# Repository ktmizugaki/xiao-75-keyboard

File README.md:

# xiao 75% keyboard

* 86 Kailh mini choc switches for keyboard keys.
* 2 Kailh X Switches for mouse buttons.
* 1 Top-up JT8P analog stick for pointing device.
* Seeed XIAO as controller.

Here is layout of xiao 75% keyboard. Darker key indicates keys with 1.25u keycap.  

I don't use `Caps Lock` key, and replaced it by `Left Control` key.

# Required parts

## Keyboard main

* 86x [Kailh PG1232 mini choc switch](https://www.aliexpress.com/item/4000277394324.html)
  * keyboard switches
* 2x [Kailh PG1425 X switch](https://www.aliexpress.com/item/32985602923.html)
  * mouse buttons
* 1x [TOP-UP JT8P-3.2T-B10K-1-16Y](https://akizukidenshi.com/catalog/g/gP-04048)
  * pointing device
* 1x [Seeed XIAO](https://akizukidenshi.com/catalog/g/gM-15178)
  * Seeed XIAO
* 88x [1N4148W](https://akizukidenshi.com/catalog/g/gI-07084)
  * SOD-123 SMD switching diode
* 4x [SS2040FL](https://akizukidenshi.com/catalog/g/gI-02073)
  * SOD-123 SMD low Vf diode
* 10x [1608Metric 560ohm SMD resistor](https://www.sengoku.co.jp/mod/sgk_cart/detail.php?code=EEHD-57GE)
* 10x [1SS355VM](https://akizukidenshi.com/catalog/g/gI-05866)
  * SOD-323 SMD switching diode
* 2x [7P pin socket](https://akizukidenshi.com/catalog/g/gP-01014)
* 1x [14P pin header](https://akizukidenshi.com/catalog/g/gC-04397)
  * split to 2x 7P pin heaeder
* 1x Keyboard PCB

## Backlight LED
* 86x [2012Metric SMD LED](https://akizukidenshi.com/catalog/g/gI-06422)
* 86x [2012Metric 2.2k ohm SMD resistor](https://www.sengoku.co.jp/mod/sgk_cart/detail.php?code=EEHD-57C4)
  * Adjust value depending on Vf of LED
* 1x [NJM12888-33](https://akizukidenshi.com/catalog/g/gI-10675)
  * SOT23-5 Voltage Regulator with enable pin
* 2x [2012Metric 0.1uF SMD capacitor](https://akizukidenshi.com/catalog/g/gP-00349)
* 1x [2012Metric 1uF SMD capacitor](https://akizukidenshi.com/catalog/g/gP-09174)
* 1x [6011S1M1 slide switch](https://akizukidenshi.com/catalog/g/gP-15365)
  * Turn on/off LEDs

# About firmware

Source code of Arduino based firmware is available under [prog](prog)

Supports only SAMD21 version of XIAO.

See [prog/README.md](prog/README.md) for details.

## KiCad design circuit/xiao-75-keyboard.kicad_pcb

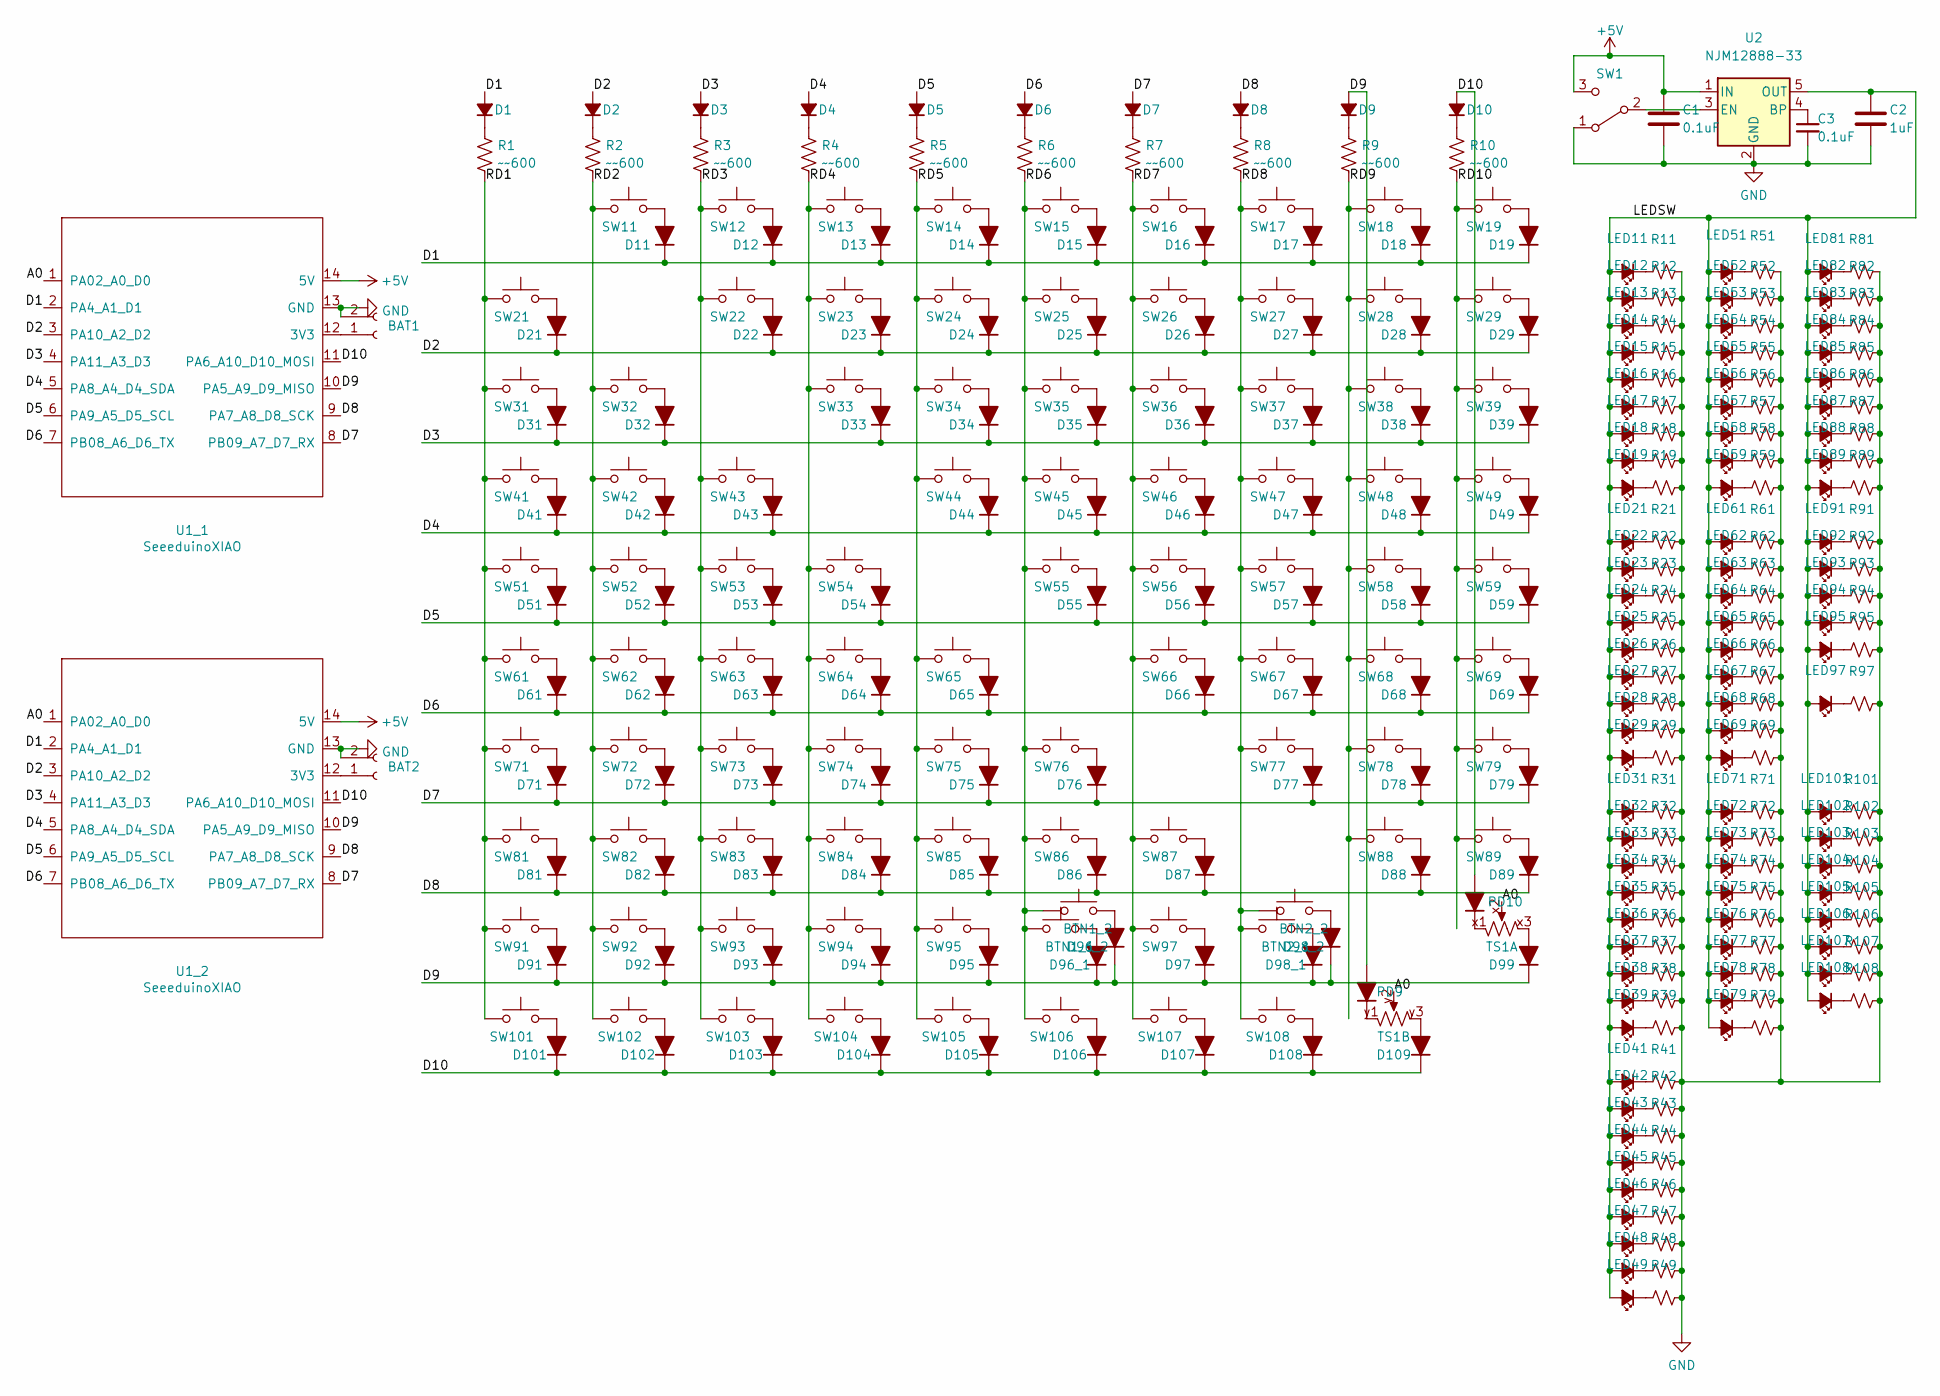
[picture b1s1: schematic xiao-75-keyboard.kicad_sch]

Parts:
BAT1, BAT2: BLEMicroPro_Battery
BTN1_1, BTN1_2: BUTTON1; Kailh_X_Switch_PG1425
BTN2_1, BTN2_2: BUTTON2; Kailh_X_Switch_PG1425
C1, C3: 0.1uF; C_0805_2012Metric_Pad1.18x1.45mm_HandSolder
C2: 1uF; C_0805_2012Metric_Pad1.18x1.45mm_HandSolder
D1, D2, D3, D4, D5, D6, D7, D8, D9, D10: 1SS355VM; D_0603_1608Metric_Pad1.05x0.95mm_HandSolder
D11, D12, D13, D14, D15, D16, D17, D18, D19, D21, D22, D23, D24, D25, D26, D27, D28, D29, D31, D32, D33, D34, D35, D36, D37, D38, D39, D41, D42, D43, D44, D45, D46, D47, D48, D49, D51, D52, D53, D54, D55, D56, D57, D58, D59, D61, D62, D63, D64, D65, D66, D67, D68, D69, D71, D72, D73, D74, D75, D76, D77, D78, D79, D81, D82, D83, D84, D85, D86, D87, D88, D89, D91, D92, D93, D94, D95, D96_1, D96_2, D97, D98_1, D98_2, D101, D102, D103, D104, D105, D106, D107, D108: 1N4148W; D_SOD-123
D99, D109: SS2040FL; D_SOD-123
LED11, LED12, LED13, LED14, LED15, LED16, LED17, LED18, LED19, LED21, LED22, LED23, LED24, LED25, LED26, LED27, LED28, LED29, LED31, LED32, LED33, LED34, LED35, LED36, LED37, LED38, LED39, LED41, LED42, LED43, LED44, LED45, LED46, LED47, LED48, LED49, LED51, LED52, LED53, LED54, LED55, LED56, LED57, LED58, LED59, LED61, LED62, LED63, LED64, LED65, LED66, LED67, LED68, LED69, LED71, LED72, LED73, LED74, LED75, LED76, LED77, LED78, LED79, LED81, LED82, LED83, LED84, LED85, LED86, LED87, LED88, LED89, LED91, LED92, LED93, LED94, LED95, LED97, LED101, LED102, LED103, LED104, LED105, LED106, LED107, LED108: 2012; LED_0805_2012Metric_Pad1.15x1.40mm_HandSolder
PD9, PD10: SS2040FL; D_SOD-123
R1, R2, R3, R4, R5, R6, R7, R8, R9, R10: ~~600; R_0603_1608Metric_Pad1.05x0.95mm_HandSolder
R11, R12, R13, R14, R15, R16, R17, R18, R19, R21, R22, R23, R24, R25, R26, R27, R28, R29, R31, R32, R33, R34, R35, R36, R37, R38, R39, R41, R42, R43, R44, R45, R46, R47, R48, R49, R51, R52, R53, R54, R55, R56, R57, R58, R59, R61, R62, R63, R64, R65, R66, R67, R68, R69, R71, R72, R73, R74, R75, R76, R77, R78, R79, R81, R82, R83, R84, R85, R86, R87, R88, R89, R91, R92, R93, R94, R95, R97, R101, R102, R103, R104, R105, R106, R107, R108: 1.5kΩ; R_0805_2012Metric_Pad1.20x1.40mm_HandSolder
SW1: 6011S1M1RE-G
SW11: ESC; Kailh_Choc_Univ
SW12: F1; Kailh_Choc_Univ
SW13: F2; Kailh_Choc_Univ
SW14: F3; Kailh_Choc_Univ
SW15: F4; Kailh_Choc_Univ
SW16: %/5; Kailh_Choc_Univ
SW17: F5; Kailh_Choc_Univ
SW18: ^/6; Kailh_Choc_Univ
SW19: F6; Kailh_Choc_Univ
SW21: Home; Kailh_Choc_Univ
SW22: DEL; Kailh_Choc_Univ
SW23: F12; Kailh_Choc_Univ
SW24: F11; Kailh_Choc_Univ
SW25: F10; Kailh_Choc_Univ
SW26: F9; Kailh_Choc_Univ
SW27: F8; Kailh_Choc_Univ
SW28: F7; Kailh_Choc_Univ
SW29: &/7; Kailh_Choc_Univ
SW31: !/1; Kailh_Choc_Univ
SW32: ~/`; Kailh_Choc_Univ
SW33: @/2; Kailh_Choc_Univ
SW34: #/3; Kailh_Choc_Univ
SW35: E; Kailh_Choc_Univ
SW36: $/4; Kailh_Choc_Univ
SW37: R; Kailh_Choc_Univ
SW38: T; Kailh_Choc_Univ
SW39: Y; Kailh_Choc_Univ
SW41: PgUp; Kailh_Choc_Univ
SW42: |/\; Kailh_Choc_Univ
SW43: BS; Kailh_Choc_Univ
SW44: +/=; Kailh_Choc_Univ
SW45: _/-; Kailh_Choc_Univ
SW46: )/0; Kailh_Choc_Univ
SW47: (/9; Kailh_Choc_Univ
SW48: */8; Kailh_Choc_Univ
SW49: U; Kailh_Choc_Univ
SW51: Q; Kailh_Choc_Univ
SW52: TAB; Kailh_Choc_Univ
SW53: W; Kailh_Choc_Univ
SW54: S; Kailh_Choc_Univ
SW55: D; Kailh_Choc_Univ
SW56: F; Kailh_Choc_Univ
SW57: G; Kailh_Choc_Univ
SW58: H; Kailh_Choc_Univ
SW59: N; Kailh_Choc_Univ
SW61: PgDn; Kailh_Choc_Univ
SW62: Enter; Kailh_Choc_Univ
SW63: }/]; Kailh_Choc_Univ
SW64: {/[; Kailh_Choc_Univ
SW65: P; Kailh_Choc_Univ
SW66: O; Kailh_Choc_Univ
SW67: K; Kailh_Choc_Univ
SW68: I; Kailh_Choc_Univ
SW69: J; Kailh_Choc_Univ
SW71: A; Kailh_Choc_Univ
SW72: CapsLock; Kailh_Choc_Univ
SW73: Z; Kailh_Choc_Univ
SW74: X; Kailh_Choc_Univ
SW75: C; Kailh_Choc_Univ
SW76: V; Kailh_Choc_Univ
SW77: B; Kailh_Choc_Univ
SW78, SW97: Space; Kailh_Choc_Univ
SW79: Alt_R; Kailh_Choc_Univ
SW81: End; Kailh_Choc_Univ
SW82: UP; Kailh_Choc_Univ
SW83: Shift_R; Kailh_Choc_Univ
SW84: "/'; Kailh_Choc_Univ
SW85: ?//; Kailh_Choc_Univ
SW86: :/;; Kailh_Choc_Univ
SW87: L; Kailh_Choc_Univ
SW88: </,; Kailh_Choc_Univ
SW89: M; Kailh_Choc_Univ
SW91: Ctrl_L; Kailh_Choc_Univ
SW92: Shift_L; Kailh_Choc_Univ
SW93: Fn; Kailh_Choc_Univ
SW94: Win_L; Kailh_Choc_Univ
SW95: Alt_L; Kailh_Choc_Univ
SW101: RIGHT; Kailh_Choc_Univ
SW102: DOWN; Kailh_Choc_Univ
SW103: LEFT; Kailh_Choc_Univ
SW104: Ctrl_R; Kailh_Choc_Univ
SW105: Fn2; Kailh_Choc_Univ
SW106: >/.; Kailh_Choc_Univ
SW107: App; Kailh_Choc_Univ
SW108: Win_R; Kailh_Choc_Univ
TS1: JT8P-3.2T-B10K-1-16Y-2; JT8P-3.2T-B10K-1-16Y
U1_1, U1_2: SeeeduinoXIAO; Seeeduino_XIAO_THT_UpsideDown
U2: NJM12888-33; SOT-23-5

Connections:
+5V: C1.1, SW1.3 (C), U1_1.14 (5V), U1_2.14 (5V), U2.1 (IN)
/A0: TS1.x2 (X), TS1.y2 (Y), U1_1.1 (PA02_A0_D0), U1_2.1 (PA02_A0_D0)
/D1: D1.2 (A), D11.1 (K), D12.1 (K), D13.1 (K), D14.1 (K), D15.1 (K), D16.1 (K), D17.1 (K), D18.1 (K), D19.1 (K), U1_1.2 (PA4_A1_D1), U1_2.2 (PA4_A1_D1)
/D2: D2.2 (A), D21.1 (K), D22.1 (K), D23.1 (K), D24.1 (K), D25.1 (K), D26.1 (K), D27.1 (K), D28.1 (K), D29.1 (K), U1_1.3 (PA10_A2_D2), U1_2.3 (PA10_A2_D2)
/D3: D3.2 (A), D31.1 (K), D32.1 (K), D33.1 (K), D34.1 (K), D35.1 (K), D36.1 (K), D37.1 (K), D38.1 (K), D39.1 (K), U1_1.4 (PA11_A3_D3), U1_2.4 (PA11_A3_D3)
/D4: D4.2 (A), D41.1 (K), D42.1 (K), D43.1 (K), D44.1 (K), D45.1 (K), D46.1 (K), D47.1 (K), D48.1 (K), D49.1 (K), U1_1.5 (PA8_A4_D4_SDA), U1_2.5 (PA8_A4_D4_SDA)
/D5: D5.2 (A), D51.1 (K), D52.1 (K), D53.1 (K), D54.1 (K), D55.1 (K), D56.1 (K), D57.1 (K), D58.1 (K), D59.1 (K), U1_1.6 (PA9_A5_D5_SCL), U1_2.6 (PA9_A5_D5_SCL)
/D6: D6.2 (A), D61.1 (K), D62.1 (K), D63.1 (K), D64.1 (K), D65.1 (K), D66.1 (K), D67.1 (K), D68.1 (K), D69.1 (K), U1_1.7 (PB08_A6_D6_TX), U1_2.7 (PB08_A6_D6_TX)
/D7: D7.2 (A), D71.1 (K), D72.1 (K), D73.1 (K), D74.1 (K), D75.1 (K), D76.1 (K), D77.1 (K), D78.1 (K), D79.1 (K), U1_1.8 (PB09_A7_D7_RX), U1_2.8 (PB09_A7_D7_RX)
/D8: D8.2 (A), D81.1 (K), D82.1 (K), D83.1 (K), D84.1 (K), D85.1 (K), D86.1 (K), D87.1 (K), D88.1 (K), D89.1 (K), U1_1.9 (PA7_A8_D8_SCK), U1_2.9 (PA7_A8_D8_SCK)
/D9: D9.2 (A), D91.1 (K), D92.1 (K), D93.1 (K), D94.1 (K), D95.1 (K), D96_1.1 (K), D96_2.1 (K), D97.1 (K), D98_1.1 (K), D98_2.1 (K), D99.1 (K), PD9.2 (A), U1_1.10 (PA5_A9_D9_MISO), U1_2.10 (PA5_A9_D9_MISO)
/D10: D10.2 (A), D101.1 (K), D102.1 (K), D103.1 (K), D104.1 (K), D105.1 (K), D106.1 (K), D107.1 (K), D108.1 (K), D109.1 (K), PD10.2 (A), U1_1.11 (PA6_A10_D10_MOSI), U1_2.11 (PA6_A10_D10_MOSI)
/LEDSW: C2.1, LED11.2 (A), LED12.2 (A), LED13.2 (A), LED14.2 (A), LED15.2 (A), LED16.2 (A), LED17.2 (A), LED18.2 (A), LED19.2 (A), LED21.2 (A), LED22.2 (A), LED23.2 (A), LED24.2 (A), LED25.2 (A), LED26.2 (A), LED27.2 (A), LED28.2 (A), LED29.2 (A), LED31.2 (A), LED32.2 (A), LED33.2 (A), LED34.2 (A), LED35.2 (A), LED36.2 (A), LED37.2 (A), LED38.2 (A), LED39.2 (A), LED41.2 (A), LED42.2 (A), LED43.2 (A), LED44.2 (A), LED45.2 (A), LED46.2 (A), LED47.2 (A), LED48.2 (A), LED49.2 (A), LED51.2 (A), LED52.2 (A), LED53.2 (A), LED54.2 (A), LED55.2 (A), LED56.2 (A), LED57.2 (A), LED58.2 (A), LED59.2 (A), LED61.2 (A), LED62.2 (A), LED63.2 (A), LED64.2 (A), LED65.2 (A), LED66.2 (A), LED67.2 (A), LED68.2 (A), LED69.2 (A), LED71.2 (A), LED72.2 (A), LED73.2 (A), LED74.2 (A), LED75.2 (A), LED76.2 (A), LED77.2 (A), LED78.2 (A), LED79.2 (A), LED81.2 (A), LED82.2 (A), LED83.2 (A), LED84.2 (A), LED85.2 (A), LED86.2 (A), LED87.2 (A), LED88.2 (A), LED89.2 (A), LED91.2 (A), LED92.2 (A), LED93.2 (A), LED94.2 (A), LED95.2 (A), LED97.2 (A), LED101.2 (A), LED102.2 (A), LED103.2 (A), LED104.2 (A), LED105.2 (A), LED106.2 (A), LED107.2 (A), LED108.2 (A), U2.5 (OUT)
/RD1: R1.2, SW21.1, SW31.1, SW41.1, SW51.1, SW61.1, SW71.1, SW81.1, SW91.1, SW101.1
/RD2: R2.2, SW11.1, SW32.1, SW42.1, SW52.1, SW62.1, SW72.1, SW82.1, SW92.1, SW102.1
/RD3: R3.2, SW12.1, SW22.1, SW43.1, SW53.1, SW63.1, SW73.1, SW83.1, SW93.1, SW103.1
/RD4: R4.2, SW13.1, SW23.1, SW33.1, SW54.1, SW64.1, SW74.1, SW84.1, SW94.1, SW104.1
/RD5: R5.2, SW14.1, SW24.1, SW34.1, SW44.1, SW65.1, SW75.1, SW85.1, SW95.1, SW105.1
/RD6: BTN1_1.2, BTN1_2.2, R6.2, SW15.1, SW25.1, SW35.1, SW45.1, SW55.1, SW76.1, SW86.1, SW106.1
/RD7: R7.2, SW16.1, SW26.1, SW36.1, SW46.1, SW56.1, SW66.1, SW87.1, SW97.1, SW107.1
/RD8: BTN2_1.2, BTN2_2.2, R8.2, SW17.1, SW27.1, SW37.1, SW47.1, SW57.1, SW67.1, SW77.1, SW108.1
/RD9: R9.2, SW18.1, SW28.1, SW38.1, SW48.1, SW58.1, SW68.1, SW78.1, SW88.1
/RD10: R10.2, SW19.1, SW29.1, SW39.1, SW49.1, SW59.1, SW69.1, SW79.1, SW89.1
GND: BAT1.2, BAT2.2, C1.2, C2.2, C3.2, R11.2, R12.2, R13.2, R14.2, R15.2, R16.2, R17.2, R18.2, R19.2, R21.2, R22.2, R23.2, R24.2, R25.2, R26.2, R27.2, R28.2, R29.2, R31.2, R32.2, R33.2, R34.2, R35.2, R36.2, R37.2, R38.2, R39.2, R41.2, R42.2, R43.2, R44.2, R45.2, R46.2, R47.2, R48.2, R49.2, R51.2, R52.2, R53.2, R54.2, R55.2, R56.2, R57.2, R58.2, R59.2, R61.2, R62.2, R63.2, R64.2, R65.2, R66.2, R67.2, R68.2, R69.2, R71.2, R72.2, R73.2, R74.2, R75.2, R76.2, R77.2, R78.2, R79.2, R81.2, R82.2, R83.2, R84.2, R85.2, R86.2, R87.2, R88.2, R89.2, R91.2, R92.2, R93.2, R94.2, R95.2, R97.2, R101.2, R102.2, R103.2, R104.2, R105.2, R106.2, R107.2, R108.2, SW1.1 (A), U1_1.13 (GND), U1_2.13 (GND), U2.2 (GND)
unnamed: BAT1.1, U1_1.12 (3V3)
unnamed: BAT2.1, U1_2.12 (3V3)
unnamed: BTN1_1.1, D96_1.2 (A)
unnamed: BTN1_2.1, D96_2.2 (A)
unnamed: BTN2_1.1, D98_1.2 (A)
unnamed: BTN2_2.1, D98_2.2 (A)
unnamed: C3.1, U2.4 (BP)
unnamed: D1.1 (K), R1.1
unnamed: D2.1 (K), R2.1
unnamed: D3.1 (K), R3.1
unnamed: D4.1 (K), R4.1
unnamed: D5.1 (K), R5.1
unnamed: D6.1 (K), R6.1
unnamed: D7.1 (K), R7.1
unnamed: D8.1 (K), R8.1
unnamed: D9.1 (K), R9.1
unnamed: D10.1 (K), R10.1
unnamed: D11.2 (A), SW11.2
unnamed: D12.2 (A), SW12.2
unnamed: D13.2 (A), SW13.2
unnamed: D14.2 (A), SW14.2
unnamed: D15.2 (A), SW15.2
unnamed: D16.2 (A), SW16.2
unnamed: D17.2 (A), SW17.2
unnamed: D18.2 (A), SW18.2
unnamed: D19.2 (A), SW19.2
unnamed: D21.2 (A), SW21.2
unnamed: D22.2 (A), SW22.2
unnamed: D23.2 (A), SW23.2
unnamed: D24.2 (A), SW24.2
unnamed: D25.2 (A), SW25.2
unnamed: D26.2 (A), SW26.2
unnamed: D27.2 (A), SW27.2
unnamed: D28.2 (A), SW28.2
unnamed: D29.2 (A), SW29.2
unnamed: D31.2 (A), SW31.2
unnamed: D32.2 (A), SW32.2
unnamed: D33.2 (A), SW33.2
unnamed: D34.2 (A), SW34.2
unnamed: D35.2 (A), SW35.2
unnamed: D36.2 (A), SW36.2
unnamed: D37.2 (A), SW37.2
unnamed: D38.2 (A), SW38.2
unnamed: D39.2 (A), SW39.2
unnamed: D41.2 (A), SW41.2
unnamed: D42.2 (A), SW42.2
unnamed: D43.2 (A), SW43.2
unnamed: D44.2 (A), SW44.2
unnamed: D45.2 (A), SW45.2
unnamed: D46.2 (A), SW46.2
unnamed: D47.2 (A), SW47.2
unnamed: D48.2 (A), SW48.2
unnamed: D49.2 (A), SW49.2
unnamed: D51.2 (A), SW51.2
unnamed: D52.2 (A), SW52.2
unnamed: D53.2 (A), SW53.2
unnamed: D54.2 (A), SW54.2
unnamed: D55.2 (A), SW55.2
unnamed: D56.2 (A), SW56.2
unnamed: D57.2 (A), SW57.2
unnamed: D58.2 (A), SW58.2
unnamed: D59.2 (A), SW59.2
unnamed: D61.2 (A), SW61.2
unnamed: D62.2 (A), SW62.2
unnamed: D63.2 (A), SW63.2
unnamed: D64.2 (A), SW64.2
unnamed: D65.2 (A), SW65.2
unnamed: D66.2 (A), SW66.2
unnamed: D67.2 (A), SW67.2
unnamed: D68.2 (A), SW68.2
unnamed: D69.2 (A), SW69.2
unnamed: D71.2 (A), SW71.2
unnamed: D72.2 (A), SW72.2
unnamed: D73.2 (A), SW73.2
unnamed: D74.2 (A), SW74.2
unnamed: D75.2 (A), SW75.2
unnamed: D76.2 (A), SW76.2
unnamed: D77.2 (A), SW77.2
unnamed: D78.2 (A), SW78.2
unnamed: D79.2 (A), SW79.2
unnamed: D81.2 (A), SW81.2
unnamed: D82.2 (A), SW82.2
unnamed: D83.2 (A), SW83.2
unnamed: D84.2 (A), SW84.2
unnamed: D85.2 (A), SW85.2
unnamed: D86.2 (A), SW86.2
unnamed: D87.2 (A), SW87.2
unnamed: D88.2 (A), SW88.2
unnamed: D89.2 (A), SW89.2
unnamed: D91.2 (A), SW91.2
unnamed: D92.2 (A), SW92.2
unnamed: D93.2 (A), SW93.2
unnamed: D94.2 (A), SW94.2
unnamed: D95.2 (A), SW95.2
unnamed: D97.2 (A), SW97.2
unnamed: D99.2 (A), TS1.x3 (GND)
unnamed: D101.2 (A), SW101.2
unnamed: D102.2 (A), SW102.2
unnamed: D103.2 (A), SW103.2
unnamed: D104.2 (A), SW104.2
unnamed: D105.2 (A), SW105.2
unnamed: D106.2 (A), SW106.2
unnamed: D107.2 (A), SW107.2
unnamed: D108.2 (A), SW108.2
unnamed: D109.2 (A), TS1.y3 (GND)
unnamed: LED11.1 (K), R11.1
unnamed: LED12.1 (K), R12.1
unnamed: LED13.1 (K), R13.1
unnamed: LED14.1 (K), R14.1
unnamed: LED15.1 (K), R15.1
unnamed: LED16.1 (K), R16.1
unnamed: LED17.1 (K), R17.1
unnamed: LED18.1 (K), R18.1
unnamed: LED19.1 (K), R19.1
unnamed: LED21.1 (K), R21.1
unnamed: LED22.1 (K), R22.1
unnamed: LED23.1 (K), R23.1
unnamed: LED24.1 (K), R24.1
unnamed: LED25.1 (K), R25.1
unnamed: LED26.1 (K), R26.1
unnamed: LED27.1 (K), R27.1
unnamed: LED28.1 (K), R28.1
unnamed: LED29.1 (K), R29.1
unnamed: LED31.1 (K), R31.1
unnamed: LED32.1 (K), R32.1
unnamed: LED33.1 (K), R33.1
unnamed: LED34.1 (K), R34.1
unnamed: LED35.1 (K), R35.1
unnamed: LED36.1 (K), R36.1
unnamed: LED37.1 (K), R37.1
unnamed: LED38.1 (K), R38.1
unnamed: LED39.1 (K), R39.1
unnamed: LED41.1 (K), R41.1
unnamed: LED42.1 (K), R42.1
unnamed: LED43.1 (K), R43.1
unnamed: LED44.1 (K), R44.1
unnamed: LED45.1 (K), R45.1
unnamed: LED46.1 (K), R46.1
unnamed: LED47.1 (K), R47.1
unnamed: LED48.1 (K), R48.1
unnamed: LED49.1 (K), R49.1
unnamed: LED51.1 (K), R51.1
unnamed: LED52.1 (K), R52.1
unnamed: LED53.1 (K), R53.1
unnamed: LED54.1 (K), R54.1
unnamed: LED55.1 (K), R55.1
unnamed: LED56.1 (K), R56.1
unnamed: LED57.1 (K), R57.1
unnamed: LED58.1 (K), R58.1
unnamed: LED59.1 (K), R59.1
unnamed: LED61.1 (K), R61.1
unnamed: LED62.1 (K), R62.1
unnamed: LED63.1 (K), R63.1
unnamed: LED64.1 (K), R64.1
unnamed: LED65.1 (K), R65.1
unnamed: LED66.1 (K), R66.1
unnamed: LED67.1 (K), R67.1
unnamed: LED68.1 (K), R68.1
unnamed: LED69.1 (K), R69.1
unnamed: LED71.1 (K), R71.1
unnamed: LED72.1 (K), R72.1
unnamed: LED73.1 (K), R73.1
unnamed: LED74.1 (K), R74.1
unnamed: LED75.1 (K), R75.1
unnamed: LED76.1 (K), R76.1
unnamed: LED77.1 (K), R77.1
unnamed: LED78.1 (K), R78.1
unnamed: LED79.1 (K), R79.1
unnamed: LED81.1 (K), R81.1
unnamed: LED82.1 (K), R82.1
unnamed: LED83.1 (K), R83.1
unnamed: LED84.1 (K), R84.1
unnamed: LED85.1 (K), R85.1
unnamed: LED86.1 (K), R86.1
unnamed: LED87.1 (K), R87.1
unnamed: LED88.1 (K), R88.1
unnamed: LED89.1 (K), R89.1
unnamed: LED91.1 (K), R91.1
unnamed: LED92.1 (K), R92.1
unnamed: LED93.1 (K), R93.1
unnamed: LED94.1 (K), R94.1
unnamed: LED95.1 (K), R95.1
unnamed: LED97.1 (K), R97.1
unnamed: LED101.1 (K), R101.1
unnamed: LED102.1 (K), R102.1
unnamed: LED103.1 (K), R103.1
unnamed: LED104.1 (K), R104.1
unnamed: LED105.1 (K), R105.1
unnamed: LED106.1 (K), R106.1
unnamed: LED107.1 (K), R107.1
unnamed: LED108.1 (K), R108.1
unnamed: PD9.1 (K), TS1.y1 (VCC)
unnamed: PD10.1 (K), TS1.x1 (VCC)
unnamed: SW1.2 (B), U2.3 (EN)

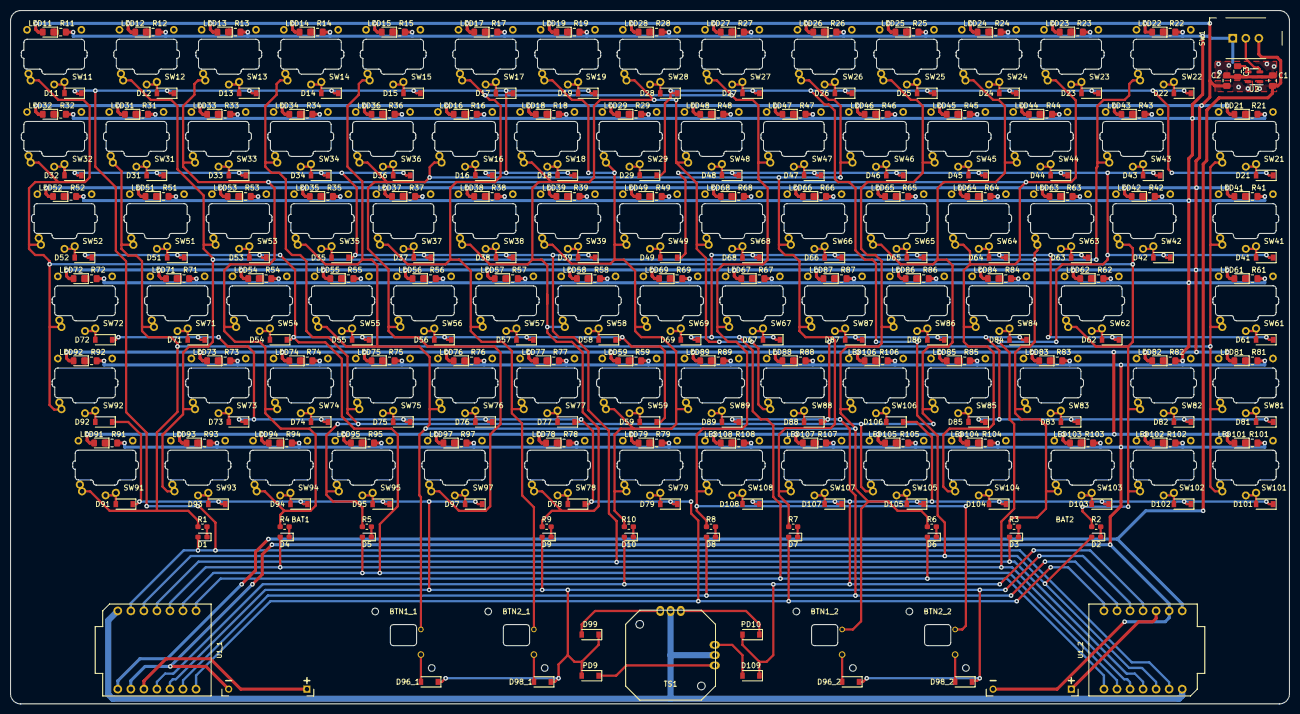
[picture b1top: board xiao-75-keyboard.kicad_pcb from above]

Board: 2 copper layers, 249.0 x 135.0 mm, 386 parts (0 on the bottom side), 218 nets.

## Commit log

2022-10-19 Add log "I got a light"
2022-10-23 Add log "Implemented switches"
2022-10-27 Add how to build firmware
2022-11-01 Add prog
2022-11-03 Add log "Completed firmware
2022-11-05 Add log "Create keycap"
2022-11-05 Add keycap
2022-11-12 Add log "Keycaps arrived"
2022-11-14 Add cap models and generator scripts
2022-11-17 Add rendered 3d model for production
2022-11-19 Add ja document
2022-11-21 Add booth text
2022-11-21 Make sketch compile with Arduino IDE
2022-11-21 Add and update prog README
2022-11-23 Enable mediakey when using HID library
2022-11-23 Improve README
2022-11-27 Rearrange texts
2022-11-30 Add images to README.ja.md
2022-12-01 Add note adventar2022
2022-12-04 Add link to previous article for advent calendar 2022
2022-12-06 Swap brightness up/down key to make it intuitive
2022-12-06 Improve description about firmware
2022-12-06 Imporve README.ja.md
2023-07-08 Clarify switches and others are not included in booth description
2023-07-08 Support extended key types whose boundary is not at 0x100
2023-07-08 Make layer keys more similar to qmk
2023-07-08 Adjust spacing of keymap
2024-01-12 Reflect name change of caps1514-all-plain.scad
2024-12-24 Show better copyright
2024-12-24 Fix position of 4th and 5th row in cap-preview
2024-12-24 Correct name of choc univ footprint
2025-01-05 Add cap model for mouse switch
2025-01-28 Add article Kailh-X-Switch-用の3Dプリントキャップを作りました
